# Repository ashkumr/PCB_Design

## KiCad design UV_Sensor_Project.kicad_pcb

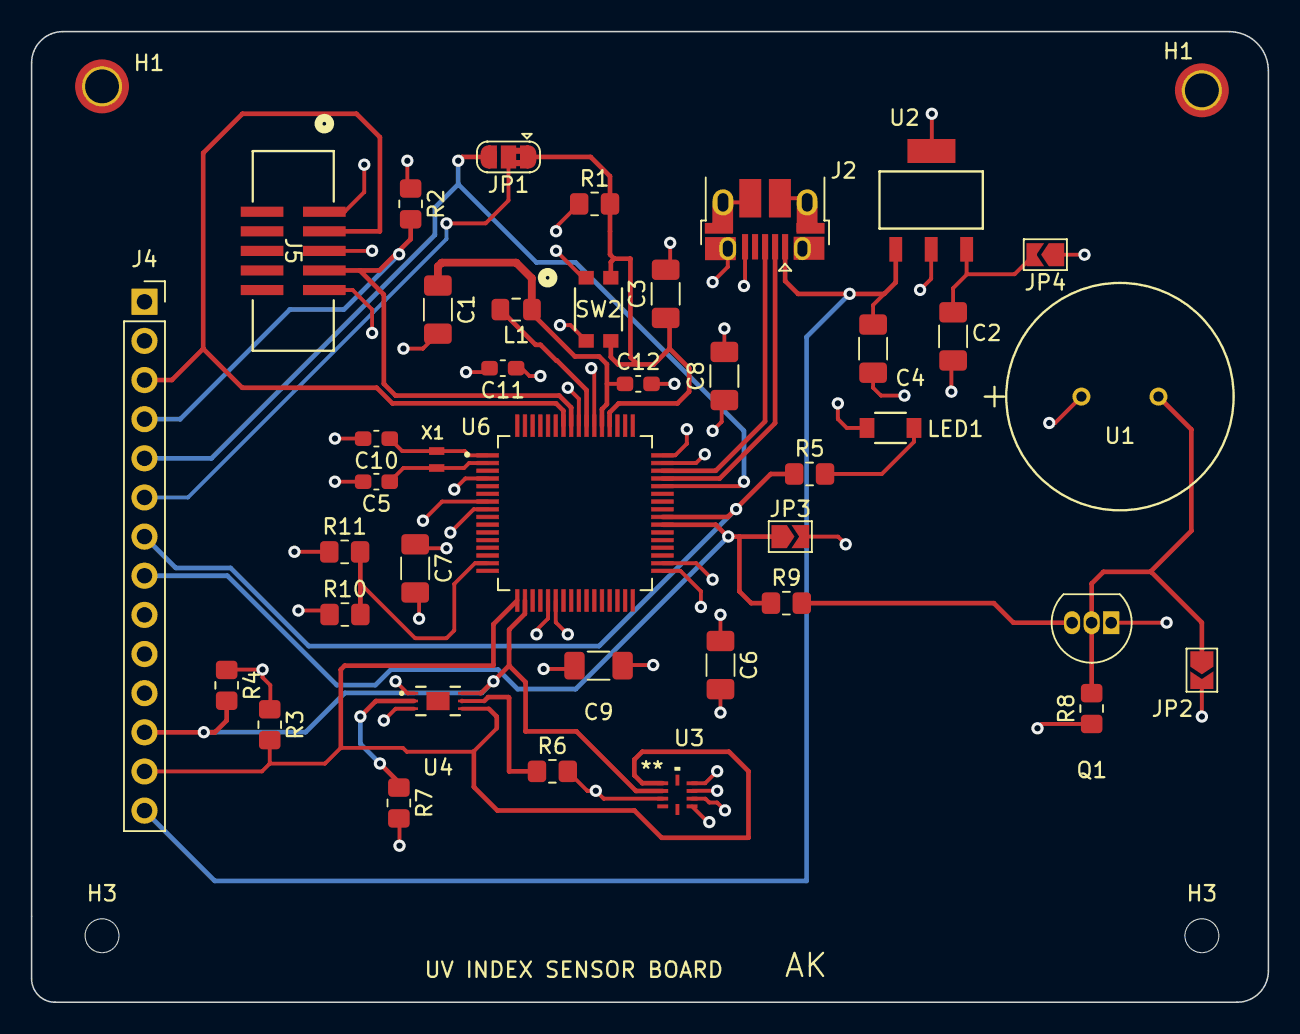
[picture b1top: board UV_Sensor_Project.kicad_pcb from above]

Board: 4 copper layers, 80.3 x 63.0 mm, 44 parts (0 on the bottom side), 25 nets.

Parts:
C1, C2, C4, C6, C7, C8, C9: 10uF; C_1206_3216Metric_Pad1.33x1.80mm_HandSolder
C3: 1uF; C_1206_3216Metric_Pad1.33x1.80mm_HandSolder
C5, C10: 9pF; C_0603_1608Metric_Pad1.08x0.95mm_HandSolder
C11, C12: 1uF; C_0603_1608Metric_Pad1.08x0.95mm_HandSolder
H1, H1#2: MountingHole_Pad; MountingHole_2.2mm_M2_ISO7380_Pad_TopBottom
H3, H3#2: MountingHole; MountingHole_2.2mm_M2_ISO7380
J2: USB_B_Micro; USB_Micro-B_Amphenol_10103594-0001LF_Horizontal
J4: Conn_01x14; PinSocket_1x14_P2.54mm_Vertical
J5: 3221-10-0300-00; CONN10_3221-10-0300-00_CNC
JP1: Bridged Jumper; SolderJumper-3_P1.3mm_Bridged2Bar12_RoundedPad1.0x1.5mm
JP2, JP3, JP4: SolderJumper_2_Open; SolderJumper-2_P1.3mm_Open_TrianglePad1.0x1.5mm
L1: 10uH; L_0805_2012Metric_Pad1.15x1.40mm_HandSolder
LED1: LTST-C150GKT; LED_LTST-C150GKT_LTO
Q1: 2SC1815; TO-92_Inline
R1, R2, R3, R4: 10K; R_0805_2012Metric_Pad1.20x1.40mm_HandSolder
R5: 100; R_0805_2012Metric_Pad1.20x1.40mm_HandSolder
R6, R8: 1K; R_0805_2012Metric_Pad1.20x1.40mm_HandSolder
R7: 4.7K; R_0805_2012Metric_Pad1.20x1.40mm_HandSolder
R9: 180; R_0805_2012Metric_Pad1.20x1.40mm_HandSolder
R10, R11: 100K; R_0805_2012Metric_Pad1.20x1.40mm_HandSolder
SW2: KMR231NGLFS; IC4_KMR231NGLFS_CNK
U1: PS1240P02CT3; SMT_PP02CT3_TDK
U2: LM3940IMP-3.3/NOPB; MP04A
U3: SI1147-A10-GMR; QFN10_2X2_SIL
U4: BH1750FVI-TR; BH1750FVI-TR_ROM
U6: SAM32_ATSAMD51J20A-AU-ATSAMD51J20A-AU; QFP50P1200X1200X120-64N
X1: ABS05-32.768KHZ-9-T; XTAL_ABS05-32.768KHZ-9-T

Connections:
+3.3V: C6.1, C7.1, C8.1, C9.1, C11.1, J4.2, J5.1, JP3.2 (B), JP4.1 (A), R1.1, R2.1, R3.1, R4.1, R6.2, R8.1, R11.1, U1.1, U3.3 (VDD), U3.6 (LED2/CVDD), U3.7 (LED3/CVDD), U3.9 (LED1), U4.1, U6.4 (PA03), U6.8 (VDDANA), U6.21 (VDDIO), U6.34 (VDDIO1), U6.48 (VDDIO2), U6.56 (VDDIO3)
/USB+: J2.3 (D+), U6.46 (PA25)
/USB-: J2.2 (D-), U6.45 (PA24)
/~RESET: C3.1, JP1.1 (A), R1.2, SW2.2, SW2.4, U6.52 (RESETN)
D14: J4.5, JP1.3 (B), U6.44 (PA23)
D14-RST: J4.6, JP1.2 (C)
D22: J4.8, JP3.1 (A), R9.1, U6.39 (PB16)
D23: J4.7, R5.1, U6.40 (PB17)
GND: C1.2, C2.2, C3.2, C4.2, C5.2, C6.2, C7.2, C8.2, C9.2, C10.2, C11.2, C12.2, J2.5 (GND), J2.6 (Shield), J4.1, J5.3, J5.5, JP2.2 (B), LED1.1, Q1.1 (E), R7.2, R10.1, SW2.1, SW2.3, U2.2 (GND), U2.4 (GND), U3.8 (GND), U4.3, U6.7 (GND), U6.22 (GND1), U6.33 (GND2), U6.47 (GND3), U6.54 (GND4)
unnamed: JP2.1 (A), Q1.2 (C), R8.2, U1.2
unnamed: C2.1, JP4.2 (B), U2.3 (OUT)
unnamed: LED1.2, R5.2
unnamed: Q1.3 (B), R9.2
unnamed: R6.1, U4.5
unnamed: R7.1, U4.2
unnamed: C10.1, U6.1 (PA00), X1.2
unnamed: C5.1, U6.2 (PA01), X1.1
unnamed: R10.2, R11.2, U6.15 (PA06)
unnamed: C1.1, C12.1, L1.1, U6.53 (VDDCORE)
unnamed: L1.2, U6.55 (VSW)
SCL: J4.12, R4.2, U3.2 (SCL), U4.6, U6.18 (PA09)
SDA: J4.13, R3.2, U3.1 (SDA), U4.4, U6.17 (PA08)
SWCLK: J4.4, J5.4, R2.2, U6.57 (PA30)
SWDIO: J4.3, J5.2, U6.58 (PA31)
VUSB: C4.1, J2.1 (VBUS), J4.14, U2.1 (IN)
